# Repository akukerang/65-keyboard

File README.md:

# 65-keyboard
- 65% keyboard PCB for PCB design practice. 
- Used masterzen's guide for keyboard design: https://www.masterzen.fr/2020/05/03/designing-a-keyboard-part-1/
- Probably not going to add LEDs, too much routing.
## Pictures
### PCB Design

### PCB Top

### PCB Bottom

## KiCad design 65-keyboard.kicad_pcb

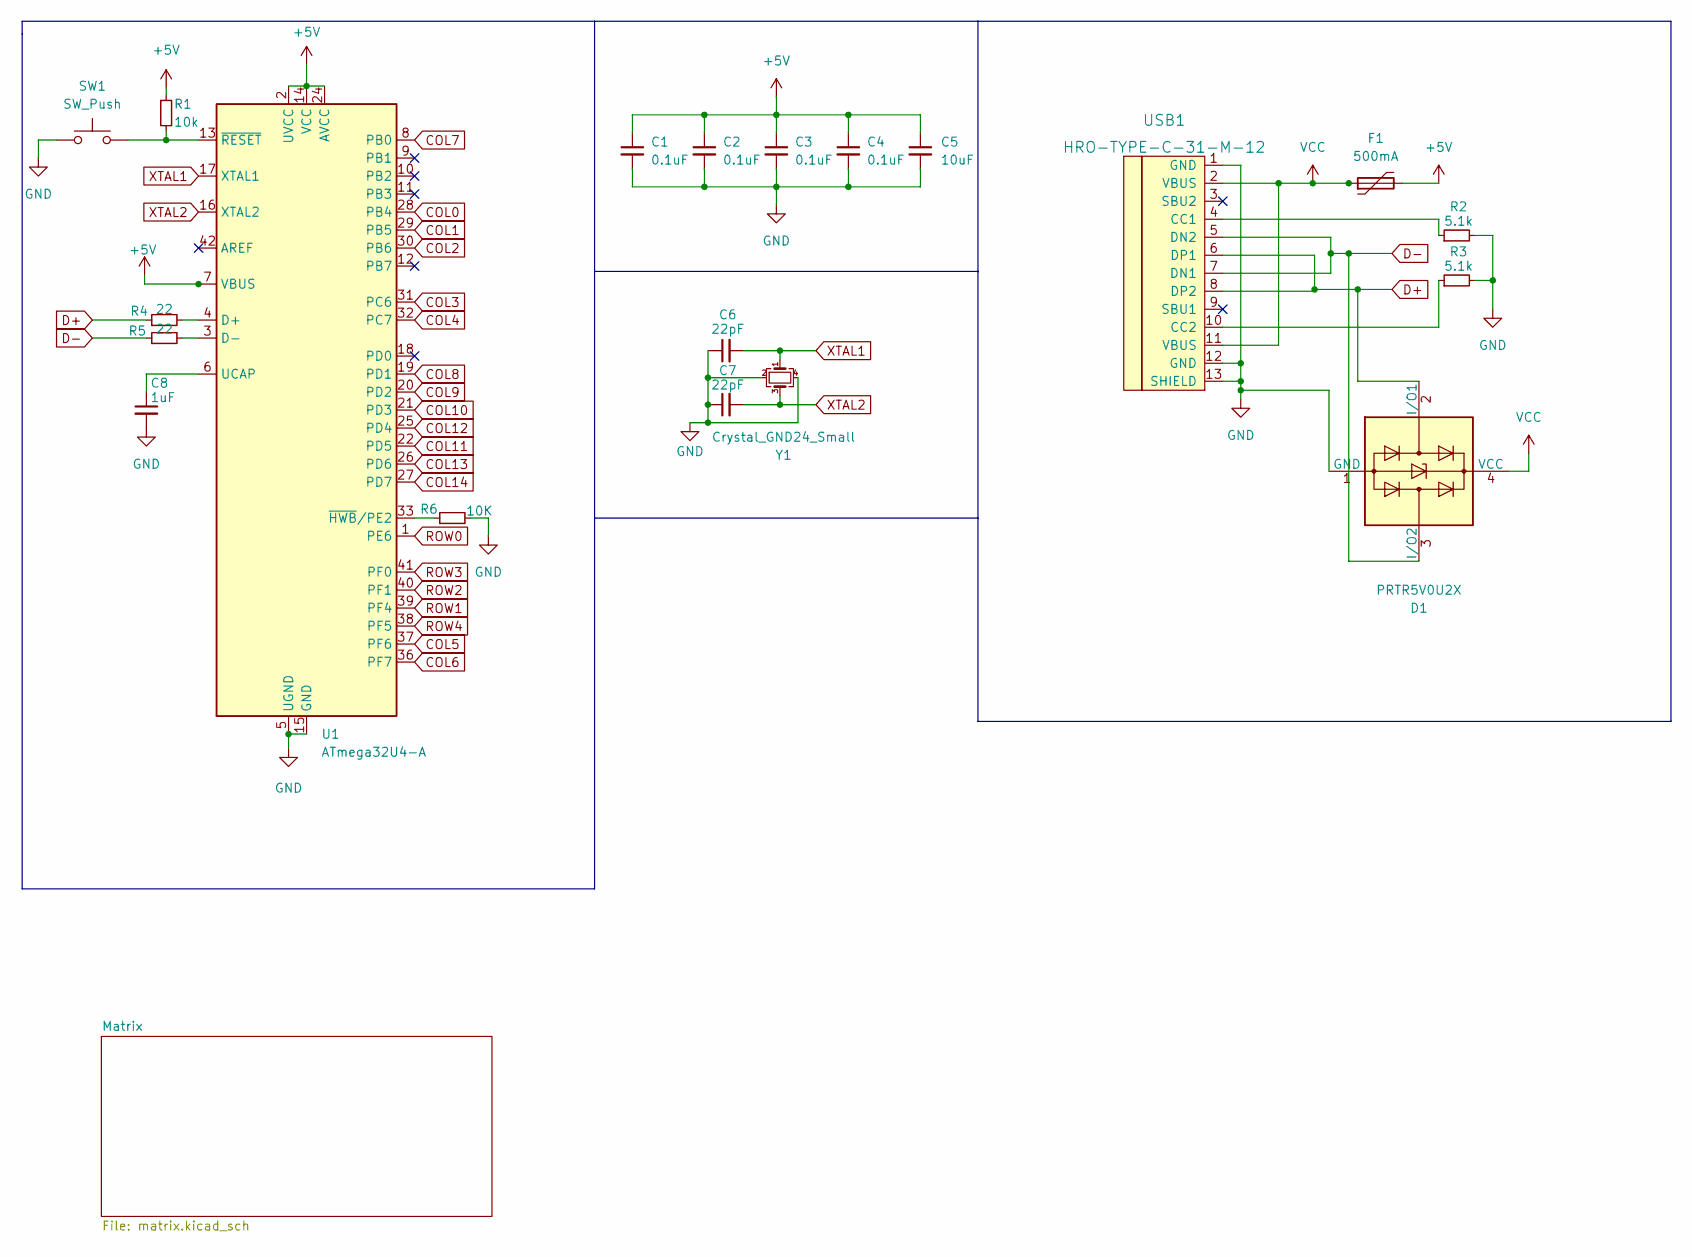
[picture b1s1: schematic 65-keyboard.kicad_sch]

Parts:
C1, C2, C3, C4: 0.1uF; C_0805_2012Metric_Pad1.18x1.45mm_HandSolder
C5: 10uF; C_0805_2012Metric_Pad1.18x1.45mm_HandSolder
C6, C7: 22pF; C_0805_2012Metric_Pad1.18x1.45mm_HandSolder
C8: 1uF; C_0805_2012Metric_Pad1.18x1.45mm_HandSolder
D1: PRTR5V0U2X; SOT143B
F1: 500mA; Fuse_1206_3216Metric_Pad1.42x1.75mm_HandSolder
R1: 10k; R_0805_2012Metric_Pad1.20x1.40mm_HandSolder
R2, R3: 5.1k; R_0805_2012Metric_Pad1.20x1.40mm_HandSolder
R4, R5: 22; R_0805_2012Metric_Pad1.20x1.40mm_HandSolder
R6: 10K; R_0805_2012Metric_Pad1.20x1.40mm_HandSolder
SW1: SW_Push; SW_SPST_SKQG_WithStem
U1: ATmega32U4-A; TQFP-44_10x10mm_P0.8mm
USB1: HRO-TYPE-C-31-M-12; HRO-TYPE-C-31-M-12-HandSoldering
Y1: Crystal_GND24_Small; Crystal_SMD_3225-4Pin_3.2x2.5mm_HandSoldering

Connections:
+5V: C1.1, C2.1, C3.1, C4.1, C5.1, F1.2, R1.1, U1.2 (UVCC), U1.7 (VBUS), U1.14 (VCC), U1.24 (AVCC), U1.34 (VCC), U1.44 (AVCC)
COL0: U1.28 (PB4); also elsewhere on the board
COL1: U1.29 (PB5); also elsewhere on the board
COL2: U1.30 (PB6); also elsewhere on the board
COL3: U1.31 (PC6); also elsewhere on the board
COL4: U1.32 (PC7); also elsewhere on the board
COL5: U1.37 (PF6); also elsewhere on the board
COL6: U1.36 (PF7); also elsewhere on the board
COL7: U1.8 (PB0); also elsewhere on the board
COL8: U1.19 (PD1); also elsewhere on the board
COL9: U1.20 (PD2); also elsewhere on the board
COL10: U1.21 (PD3); also elsewhere on the board
COL11: U1.22 (PD5); also elsewhere on the board
COL12: U1.25 (PD4); also elsewhere on the board
COL13: U1.26 (PD6); also elsewhere on the board
COL14: U1.27 (PD7); also elsewhere on the board
D+: D1.2 (I/O1), R4.1, USB1.6 (DP1), USB1.8 (DP2)
D-: D1.3 (I/O2), R5.1, USB1.5 (DN2), USB1.7 (DN1)
GND: C1.2, C2.2, C3.2, C4.2, C5.2, C6.1, C7.1, C8.2, D1.1 (GND), R2.2, R3.2, R6.2, SW1.1, U1.5 (UGND), U1.15 (GND), U1.23 (GND), U1.35 (GND), U1.43 (GND), USB1.1 (GND), USB1.12 (GND), USB1.13 (SHIELD), Y1.2, Y1.4
unnamed: C8.1, U1.6 (UCAP)
unnamed: R1.2, SW1.2, U1.13 (~RESET)
unnamed: R2.1, USB1.4 (CC1)
unnamed: R3.1, USB1.10 (CC2)
unnamed: R4.2, U1.4 (D+)
unnamed: R5.2, U1.3 (D-)
unnamed: R6.1, U1.33 (~HWB/PE2)
ROW0: U1.1 (PE6); also elsewhere on the board
ROW1: U1.39 (PF4); also elsewhere on the board
ROW2: U1.40 (PF1); also elsewhere on the board
ROW3: U1.41 (PF0); also elsewhere on the board
ROW4: U1.38 (PF5); also elsewhere on the board
VCC: D1.4 (VCC), F1.1, USB1.2 (VBUS), USB1.11 (VBUS)
XTAL1: C6.2, U1.17 (XTAL1), Y1.1
XTAL2: C7.2, U1.16 (XTAL2), Y1.3

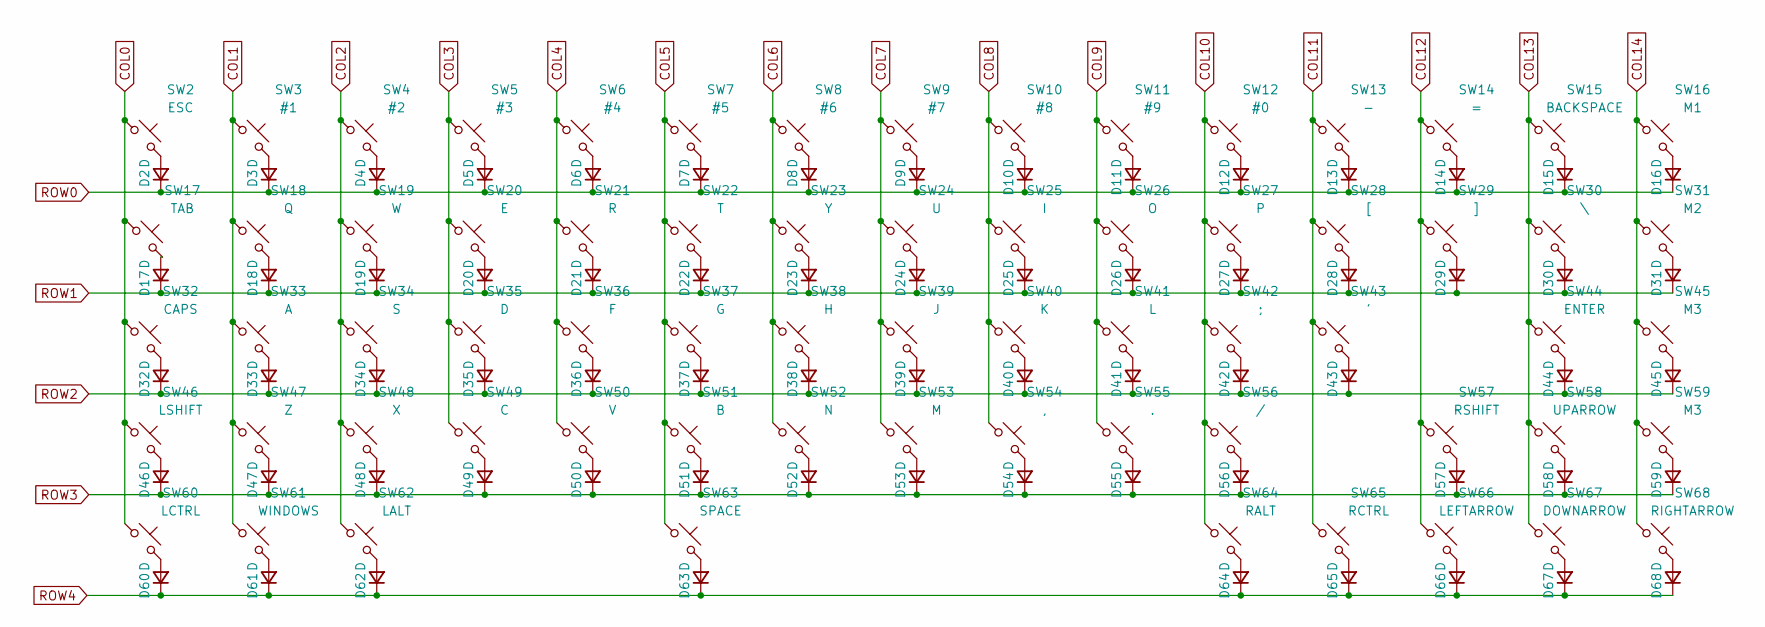
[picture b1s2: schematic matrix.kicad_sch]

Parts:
D2, D3, D4, D5, D6, D7, D8, D9, D10, D11, D12, D13, D14, D15, D16, D17, D18, D19, D20, D21, D22, D23, D24, D25, D26, D27, D28, D29, D30, D31, D32, D33, D34, D35, D36, D37, D38, D39, D40, D41, D42, D43, D44, D45, D46, D47, D48, D49, D50, D51, D52, D53, D54, D55, D56, D57, D58, D59, D60, D61, D62, D63, D64, D65, D66, D67, D68: D; D_SOD-123
SW2: ESC; SW_MX_1u
SW3: #1; SW_MX_1u
SW4: #2; SW_MX_1u
SW5: #3; SW_MX_1u
SW6: #4; SW_MX_1u
SW7: #5; SW_MX_1u
SW8: #6; SW_MX_1u
SW9: #7; SW_MX_1u
SW10: #8; SW_MX_1u
SW11: #9; SW_MX_1u
SW12: #0; SW_MX_1u
SW13: -; SW_MX_1u
SW14: =; SW_MX_1u
SW15: BACKSPACE; SW_MX_1u
SW16: M1; SW_MX_1u
SW17: TAB; SW_MX_1.5u
SW18: Q; SW_MX_1u
SW19: W; SW_MX_1u
SW20: E; SW_MX_1u
SW21: R; SW_MX_1u
SW22: T; SW_MX_1u
SW23: Y; SW_MX_1u
SW24: U; SW_MX_1u
SW25: I; SW_MX_1u
SW26: O; SW_MX_1u
SW27: P; SW_MX_1u
SW28: [; SW_MX_1u
SW29: ]; SW_MX_1u
SW30: \; SW_MX_1.5u
SW31: M2; SW_MX_1u
SW32: CAPS; SW_MX_1.75u
SW33: A; SW_MX_1u
SW34: S; SW_MX_1u
SW35: D; SW_MX_1u
SW36: F; SW_MX_1u
SW37: G; SW_MX_1u
SW38: H; SW_MX_1u
SW39: J; SW_MX_1u
SW40: K; SW_MX_1u
SW41: L; SW_MX_1u
SW42: ;; SW_MX_1u
SW43: '; SW_MX_1u
SW44: ENTER; SW_MX_1u
SW45, SW59: M3; SW_MX_1u
SW46: LSHIFT; SW_MX_1u
SW47: Z; SW_MX_1u
SW48: X; SW_MX_1u
SW49: C; SW_MX_1u
SW50: V; SW_MX_1u
SW51: B; SW_MX_1u
SW52: N; SW_MX_1u
SW53: M; SW_MX_1u
SW54: ,; SW_MX_1u
SW55: .; SW_MX_1u
SW56: /; SW_MX_1u
SW57: RSHIFT; SW_MX_1.75u
SW58: UPARROW; SW_MX_1u
SW60: LCTRL; SW_MX_1.25u
SW61: WINDOWS; SW_MX_1.25u
SW62: LALT; SW_MX_1.25u
SW63: SPACE; SW_MX_1u
SW64: RALT; SW_MX_1.25u
SW65: RCTRL; SW_MX_1.25u
SW66: LEFTARROW; SW_MX_1u
SW67: DOWNARROW; SW_MX_1u
SW68: RIGHTARROW; SW_MX_1u

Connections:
COL0: SW2.1, SW17.1, SW32.1, SW46.1, SW60.1; also elsewhere on the board
COL1: SW3.1, SW18.1, SW33.1, SW47.1, SW61.1; also elsewhere on the board
COL2: SW4.1, SW19.1, SW34.1, SW48.1, SW62.1; also elsewhere on the board
COL3: SW5.1, SW20.1, SW35.1, SW49.1; also elsewhere on the board
COL4: SW6.1, SW21.1, SW36.1, SW50.1; also elsewhere on the board
COL5: SW7.1, SW22.1, SW37.1, SW51.1, SW63.1; also elsewhere on the board
COL6: SW8.1, SW23.1, SW38.1, SW52.1; also elsewhere on the board
COL7: SW9.1, SW24.1, SW39.1, SW53.1; also elsewhere on the board
COL8: SW10.1, SW25.1, SW40.1, SW54.1; also elsewhere on the board
COL9: SW11.1, SW26.1, SW41.1, SW55.1; also elsewhere on the board
COL10: SW12.1, SW27.1, SW42.1, SW56.1, SW64.1; also elsewhere on the board
COL11: SW13.1, SW28.1, SW43.1, SW65.1; also elsewhere on the board
COL12: SW14.1, SW29.1, SW57.1, SW66.1; also elsewhere on the board
COL13: SW15.1, SW30.1, SW44.1, SW58.1, SW67.1; also elsewhere on the board
COL14: SW16.1, SW31.1, SW45.1, SW59.1, SW68.1; also elsewhere on the board
unnamed: D2.2 (A), SW2.2
unnamed: D3.2 (A), SW3.2
unnamed: D4.2 (A), SW4.2
unnamed: D5.2 (A), SW5.2
unnamed: D6.2 (A), SW6.2
unnamed: D7.2 (A), SW7.2
unnamed: D8.2 (A), SW8.2
unnamed: D9.2 (A), SW9.2
unnamed: D10.2 (A), SW10.2
unnamed: D11.2 (A), SW11.2
unnamed: D12.2 (A), SW12.2
unnamed: D13.2 (A), SW13.2
unnamed: D14.2 (A), SW14.2
unnamed: D15.2 (A), SW15.2
unnamed: D16.2 (A), SW16.2
unnamed: D17.2 (A), SW17.2
unnamed: D18.2 (A), SW18.2
unnamed: D19.2 (A), SW19.2
unnamed: D20.2 (A), SW20.2
unnamed: D21.2 (A), SW21.2
unnamed: D22.2 (A), SW22.2
unnamed: D23.2 (A), SW23.2
unnamed: D24.2 (A), SW24.2
unnamed: D25.2 (A), SW25.2
unnamed: D26.2 (A), SW26.2
unnamed: D27.2 (A), SW27.2
unnamed: D28.2 (A), SW28.2
unnamed: D29.2 (A), SW29.2
unnamed: D30.2 (A), SW30.2
unnamed: D31.2 (A), SW31.2
unnamed: D32.2 (A), SW32.2
unnamed: D33.2 (A), SW33.2
unnamed: D34.2 (A), SW34.2
unnamed: D35.2 (A), SW35.2
unnamed: D36.2 (A), SW36.2
unnamed: D37.2 (A), SW37.2
unnamed: D38.2 (A), SW38.2
unnamed: D39.2 (A), SW39.2
unnamed: D40.2 (A), SW40.2
unnamed: D41.2 (A), SW41.2
unnamed: D42.2 (A), SW42.2
unnamed: D43.2 (A), SW43.2
unnamed: D44.2 (A), SW44.2
unnamed: D45.2 (A), SW45.2
unnamed: D46.2 (A), SW46.2
unnamed: D47.2 (A), SW47.2
unnamed: D48.2 (A), SW48.2
unnamed: D49.2 (A), SW49.2
unnamed: D50.2 (A), SW50.2
unnamed: D51.2 (A), SW51.2
unnamed: D52.2 (A), SW52.2
unnamed: D53.2 (A), SW53.2
unnamed: D54.2 (A), SW54.2
unnamed: D55.2 (A), SW55.2
unnamed: D56.2 (A), SW56.2
unnamed: D57.2 (A), SW57.2
unnamed: D58.2 (A), SW58.2
unnamed: D59.2 (A), SW59.2
unnamed: D60.2 (A), SW60.2
unnamed: D61.2 (A), SW61.2
unnamed: D62.2 (A), SW62.2
unnamed: D63.2 (A), SW63.2
unnamed: D64.2 (A), SW64.2
unnamed: D65.2 (A), SW65.2
unnamed: D66.2 (A), SW66.2
unnamed: D67.2 (A), SW67.2
unnamed: D68.2 (A), SW68.2
ROW0: D2.1 (K), D3.1 (K), D4.1 (K), D5.1 (K), D6.1 (K), D7.1 (K), D8.1 (K), D9.1 (K), D10.1 (K), D11.1 (K), D12.1 (K), D13.1 (K), D14.1 (K), D15.1 (K), D16.1 (K); also elsewhere on the board
ROW1: D17.1 (K), D18.1 (K), D19.1 (K), D20.1 (K), D21.1 (K), D22.1 (K), D23.1 (K), D24.1 (K), D25.1 (K), D26.1 (K), D27.1 (K), D28.1 (K), D29.1 (K), D30.1 (K), D31.1 (K); also elsewhere on the board
ROW2: D32.1 (K), D33.1 (K), D34.1 (K), D35.1 (K), D36.1 (K), D37.1 (K), D38.1 (K), D39.1 (K), D40.1 (K), D41.1 (K), D42.1 (K), D43.1 (K), D44.1 (K), D45.1 (K); also elsewhere on the board
ROW3: D46.1 (K), D47.1 (K), D48.1 (K), D49.1 (K), D50.1 (K), D51.1 (K), D52.1 (K), D53.1 (K), D54.1 (K), D55.1 (K), D56.1 (K), D57.1 (K), D58.1 (K), D59.1 (K); also elsewhere on the board
ROW4: D60.1 (K), D61.1 (K), D62.1 (K), D63.1 (K), D64.1 (K), D65.1 (K), D66.1 (K), D67.1 (K), D68.1 (K); also elsewhere on the board

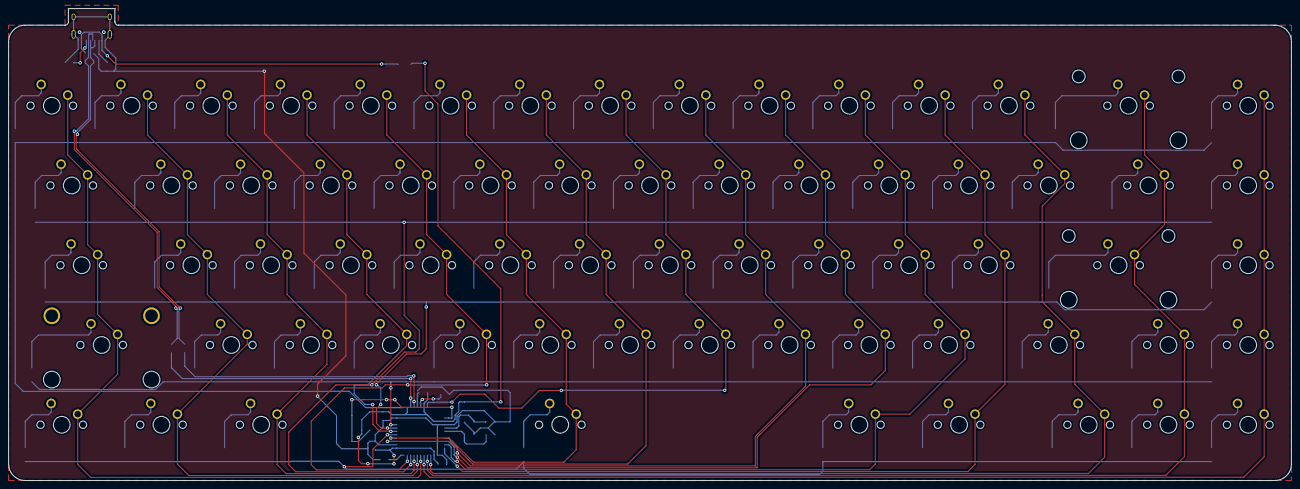
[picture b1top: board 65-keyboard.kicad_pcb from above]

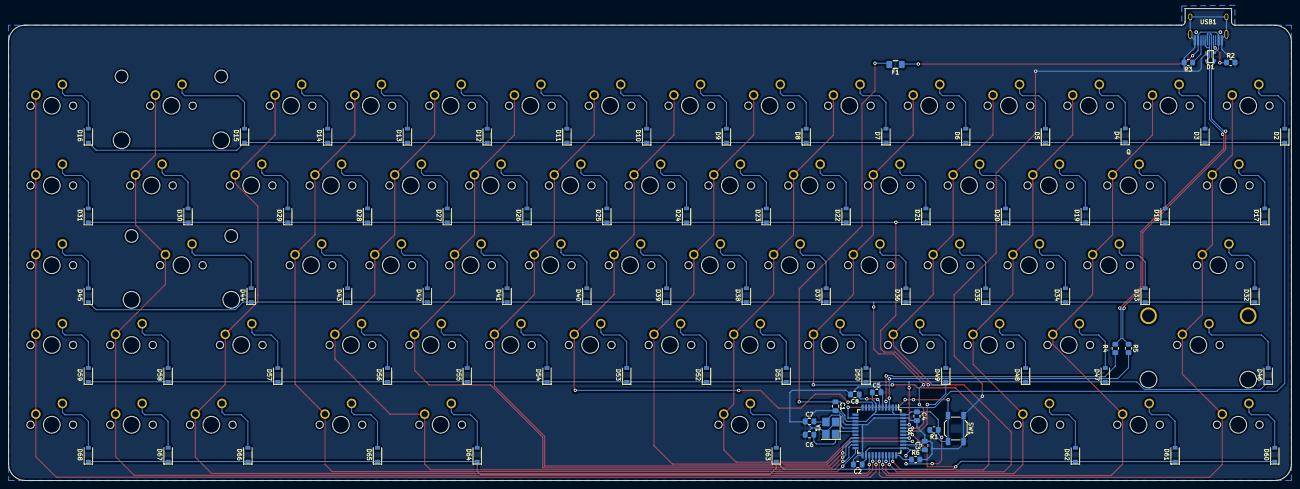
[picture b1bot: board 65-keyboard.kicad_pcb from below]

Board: 2 copper layers, 306.4 x 112.7 mm, 154 parts (154 on the bottom side), 101 nets.

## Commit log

2022-07-03 Init commit
2022-07-03 Added submodules
2022-07-03 Schematic progress
    MCU, USB-C, Crystal done. Also added USB-C submodule.
2022-07-03 Matrix Schematic
2022-07-03 MCU Schematic Finish
2022-07-04 PCB start, schematic mostly finished
2022-07-04 PCB Outline
    Switches placed in correct areas mostly. Still need to route and place components.
2022-07-04 more routing
2022-07-05 routing "finished"
    DRC still returns issues, but routing is done.
2022-07-06 rerouted pcb
    fixing drc issues
2022-07-06 readding submodules
2022-07-06 Readded submodules
2022-07-06 More routing
    Still need to connect all the 5v and GND
2022-07-07 PCB Routing finish
2022-07-07 routing extras
2022-07-07 USB-C 3D model
    Added USB-C 3d model to the footprint in 3d viewer
2022-07-07 read.me init commit
